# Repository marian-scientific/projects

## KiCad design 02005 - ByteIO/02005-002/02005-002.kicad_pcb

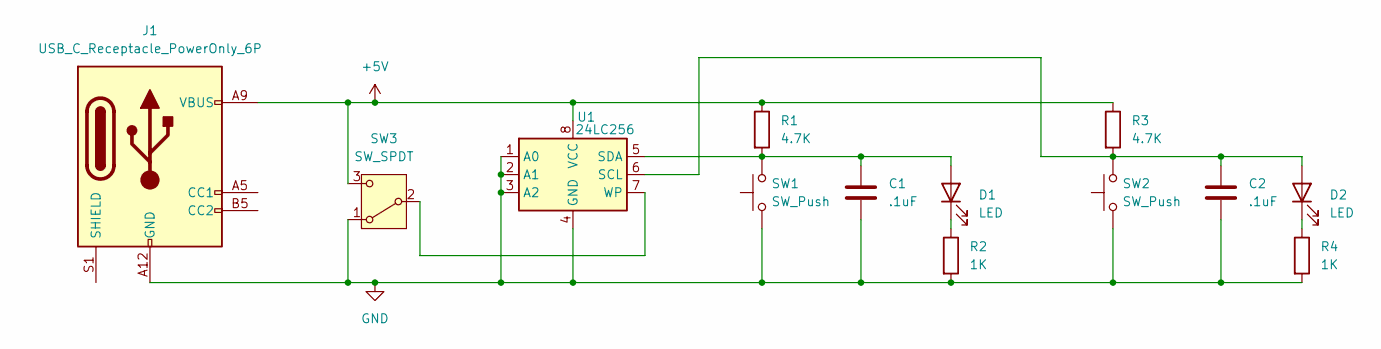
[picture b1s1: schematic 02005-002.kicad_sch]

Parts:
C1, C2: .1uF; C_1206_3216Metric
D1, D2: LED; LED_1206_3216Metric
J1: USB_C_Receptacle_PowerOnly_6P; USB_C_Receptacle_GCT_USB4125-xx-x_6P_TopMnt_Horizontal
R1, R3: 4.7K; R_1206_3216Metric
R2, R4: 1K; R_1206_3216Metric
SW1, SW2: SW_Push; SW_PUSH_6mm_H5mm
SW3: SW_SPDT; SW_Slide-03_Wuerth-WS-SLTV_10x2.5x6.4_P2.54mm
U1: 24LC256; SOIC-8_3.9x4.9mm_P1.27mm

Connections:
+5V: J1.A9 (VBUS), J1.B9 (VBUS), R1.1, R3.1, SW3.3 (C), U1.8 (VCC)
GND: C1.2, C2.2, J1.A12 (GND), J1.B12 (GND), J1.S1 (SHIELD), R2.2, R4.2, SW1.1, SW2.1, SW3.1 (A), U1.1 (A0), U1.2 (A1), U1.3 (A2), U1.4 (GND)
unnamed: C1.1, D1.2 (A), R1.2, SW1.2, U1.5 (SDA)
unnamed: D1.1 (K), R2.1
unnamed: C2.1, D2.2 (A), R3.2, SW2.2, U1.6 (SCL)
unnamed: D2.1 (K), R4.1
unnamed: SW3.2 (B), U1.7 (WP)

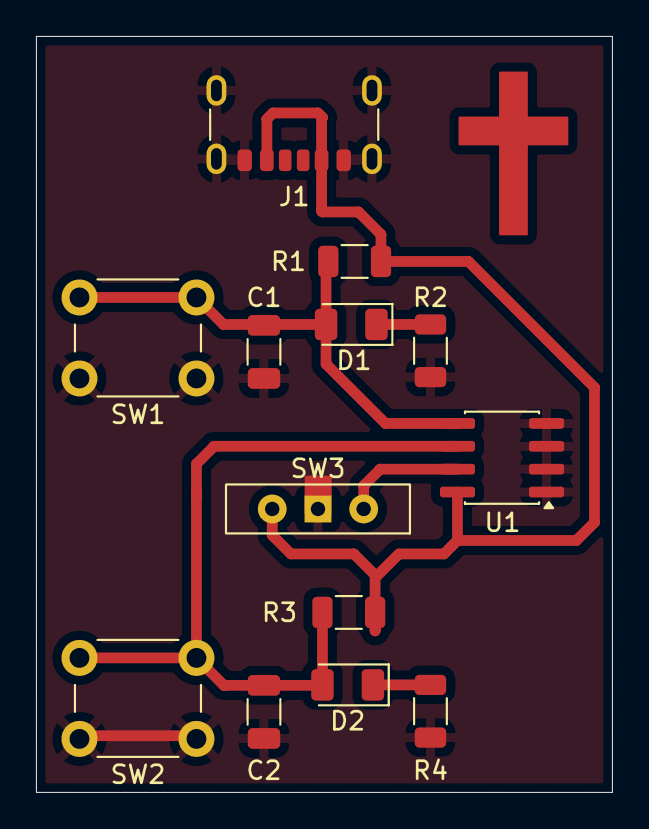
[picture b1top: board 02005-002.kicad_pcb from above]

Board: 2 copper layers, 32.0 x 42.0 mm, 13 parts (0 on the bottom side), 7 nets.

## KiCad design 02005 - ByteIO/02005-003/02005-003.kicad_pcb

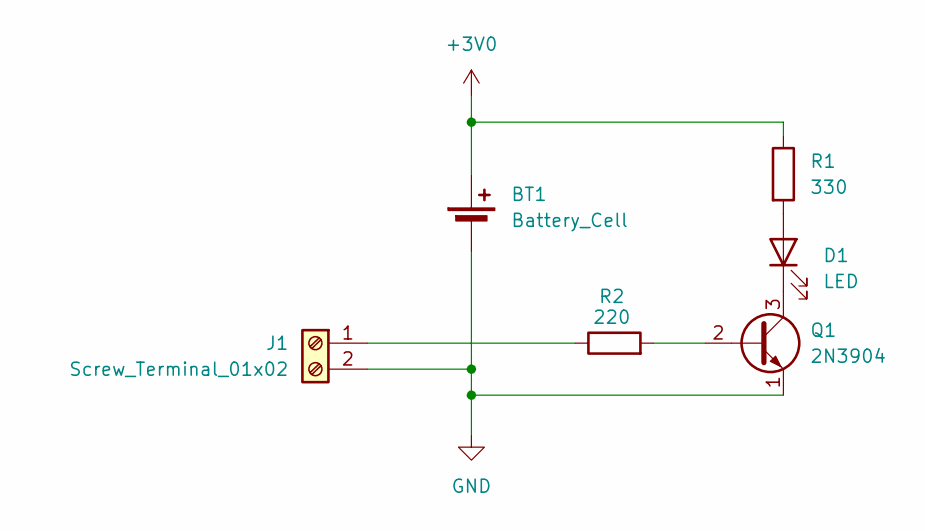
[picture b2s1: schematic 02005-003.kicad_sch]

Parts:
BT1: Battery_Cell; BatteryHolder_Keystone_1058_1x2032
D1: LED; LED_1206_3216Metric
J1: Screw_Terminal_01x02; TerminalBlock_Phoenix_MPT-0,5-2-2.54_1x02_P2.54mm_Horizontal
Q1: 2N3904; SOT-23
R1: 330; R_1206_3216Metric
R2: 220; R_1206_3216Metric

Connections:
+3V0: BT1.1 (+), R1.1
GND: BT1.2 (-), J1.2, Q1.1 (E)
unnamed: D1.2 (A), R1.2
unnamed: D1.1 (K), Q1.3 (C)
unnamed: J1.1, R2.1
unnamed: Q1.2 (B), R2.2

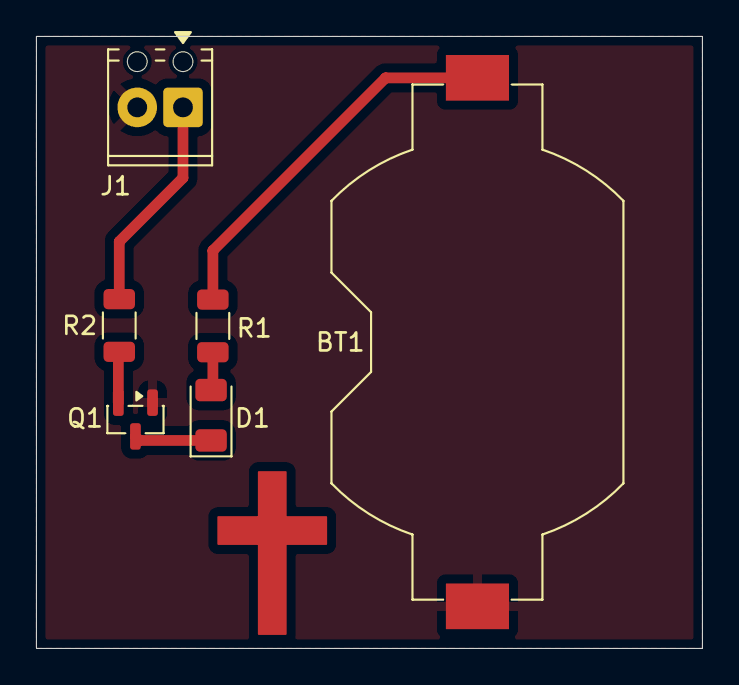
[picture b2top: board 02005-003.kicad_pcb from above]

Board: 2 copper layers, 37.0 x 34.0 mm, 6 parts (0 on the bottom side), 6 nets.

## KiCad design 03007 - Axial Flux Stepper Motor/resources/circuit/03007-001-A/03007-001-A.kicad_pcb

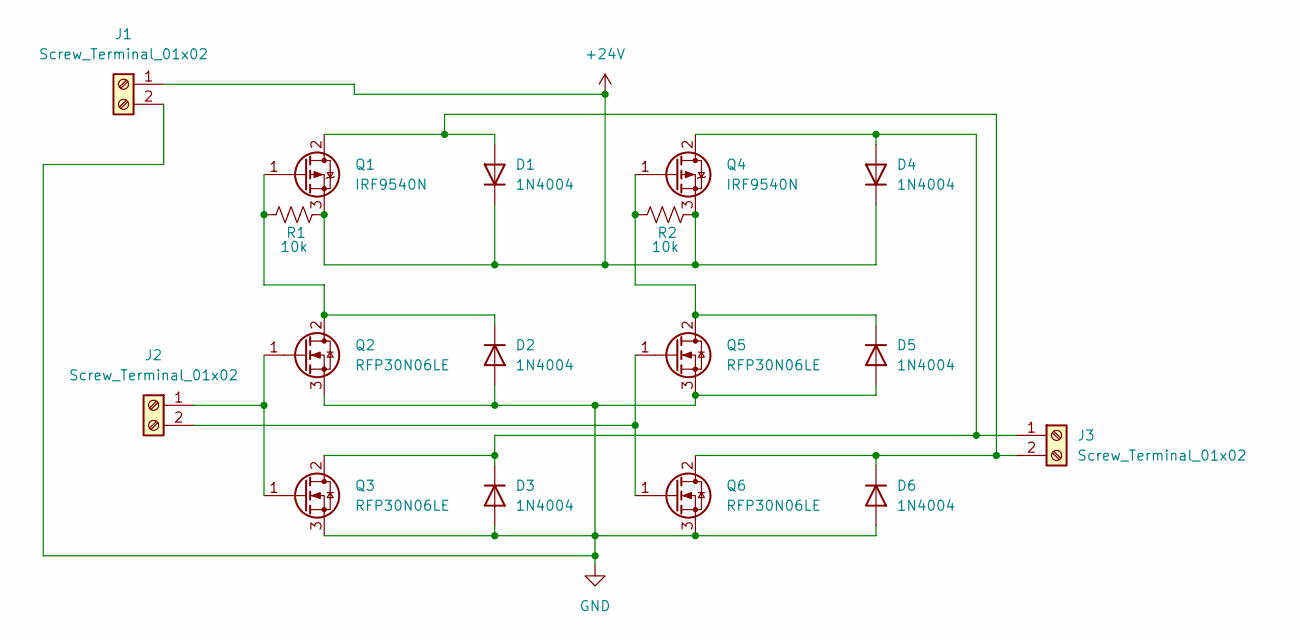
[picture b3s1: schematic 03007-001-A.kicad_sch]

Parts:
D1, D2, D3, D4, D5, D6: 1N4004; D_DO-41_SOD81_P10.16mm_Horizontal
J1, J2, J3: Screw_Terminal_01x02; TerminalBlock_TE_282834-2_1x02_P2.54mm_Horizontal
Q1, Q4: IRF9540N; TO-220-3_Vertical
Q2, Q3, Q5, Q6: RFP30N06LE; TO-220-3_Vertical
R1, R2: 10k; R_Axial_DIN0207_L6.3mm_D2.5mm_P10.16mm_Horizontal

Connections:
+24V: D1.1 (K), D4.1 (K), J1.1, Q1.3 (S), Q4.3 (S), R1.2, R2.2
GND: D2.2 (A), D3.2 (A), D5.2 (A), D6.2 (A), J1.2, Q2.3 (S), Q3.3 (S), Q5.3 (S), Q6.3 (S)
unnamed: D1.2 (A), D6.1 (K), J3.2, Q1.2 (D), Q6.2 (D)
unnamed: D2.1 (K), Q1.1 (G), Q2.2 (D), R1.1
unnamed: D3.1 (K), D4.2 (A), J3.1, Q3.2 (D), Q4.2 (D)
unnamed: D5.1 (K), Q4.1 (G), Q5.2 (D), R2.1
unnamed: J2.1, Q2.1 (G), Q3.1 (G)
unnamed: J2.2, Q5.1 (G), Q6.1 (G)

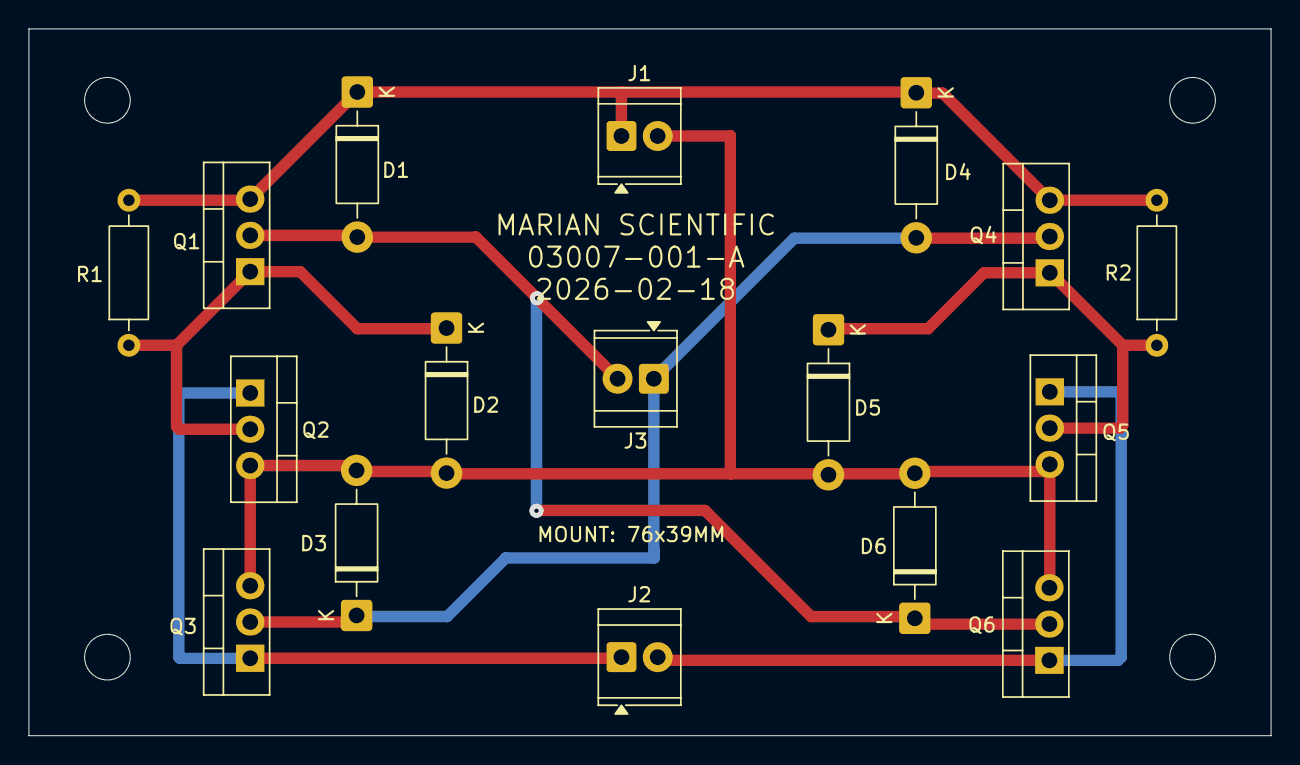
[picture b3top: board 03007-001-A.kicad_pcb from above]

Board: 2 copper layers, 87.0 x 49.5 mm, 17 parts (0 on the bottom side), 8 nets.

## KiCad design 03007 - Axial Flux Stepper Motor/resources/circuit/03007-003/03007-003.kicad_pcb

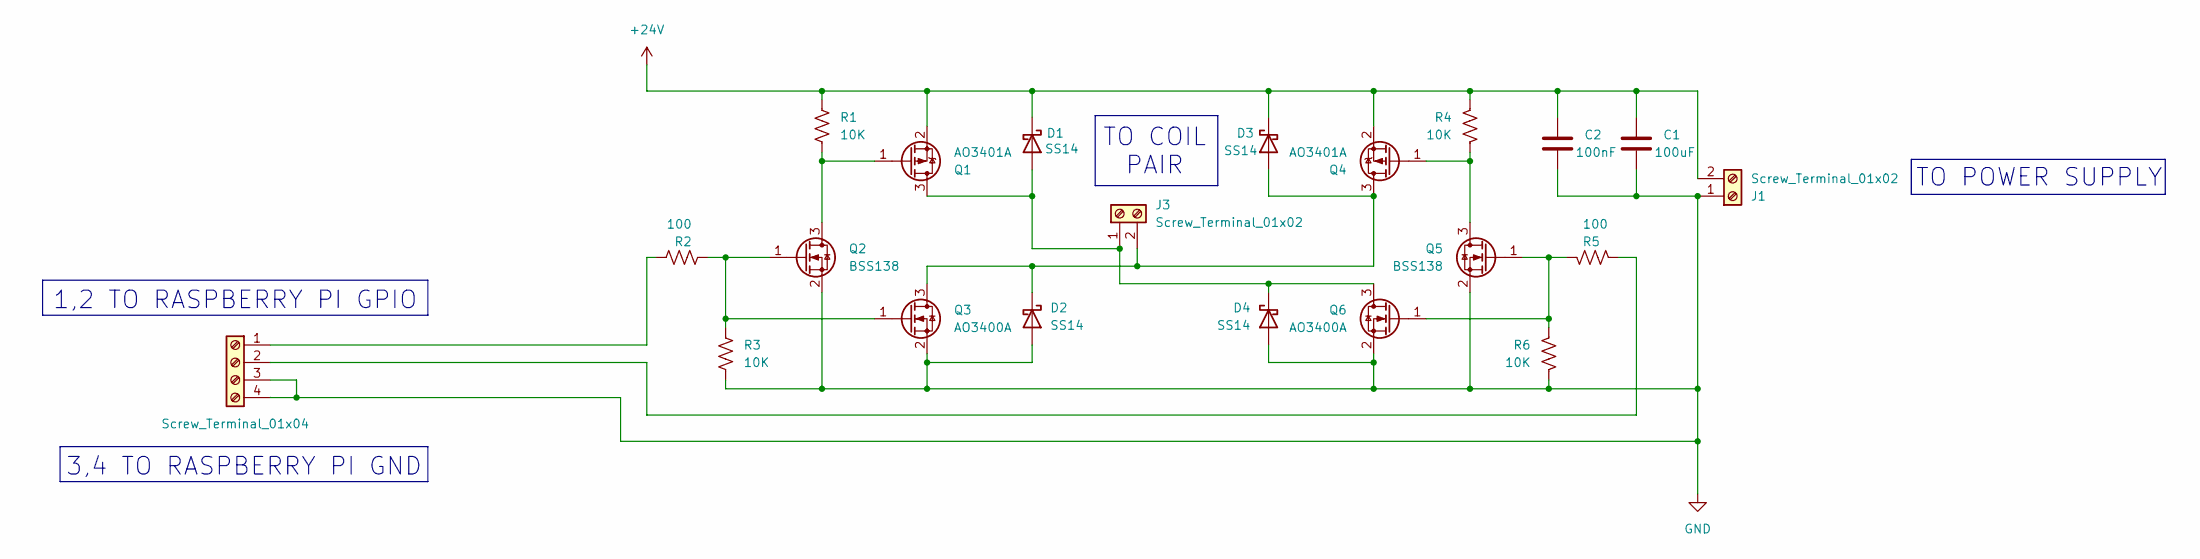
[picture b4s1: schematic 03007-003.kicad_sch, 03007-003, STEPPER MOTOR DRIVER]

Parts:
C1: 100uF; CP_Radial_D5.0mm_P2.50mm
C2: 100nF; C_Disc_D5.0mm_W2.5mm_P2.50mm
D1, D2, D3, D4: SS14; D_SMA
J1, J3: Screw_Terminal_01x02; TerminalBlock_Phoenix_PT-1,5-2-5.0-H_1x02_P5.00mm_Horizontal
J2: Screw_Terminal_01x04; TerminalBlock_Phoenix_MPT-0,5-4-2.54_1x04_P2.54mm_Horizontal
Q1, Q4: AO3401A; SOT-23
Q2, Q5: BSS138; SOT-23
Q3, Q6: AO3400A; SOT-23
R1, R3, R4, R6: 10K; R_1206_3216Metric
R2, R5: 100; R_1206_3216Metric

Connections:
+24V: C1.1, C2.1, D1.1 (K), D3.1 (K), J1.2, Q1.2 (S), Q4.2 (S), R1.1, R4.1
GND: C1.2, C2.2, D2.2 (A), D4.2 (A), J1.1, J2.3, J2.4, Q2.2 (S), Q3.2 (S), Q5.2 (S), Q6.2 (S), R3.2, R6.2
unnamed: D1.2 (A), D4.1 (K), J3.1, Q1.3 (D), Q6.3 (D)
unnamed: D2.1 (K), D3.2 (A), J3.2, Q3.3 (D), Q4.3 (D)
unnamed: J2.1, R2.1
unnamed: J2.2, R5.1
unnamed: Q1.1 (G), Q2.3 (D), R1.2
unnamed: Q2.1 (G), Q3.1 (G), R2.2, R3.1
unnamed: Q4.1 (G), Q5.3 (D), R4.2
unnamed: Q5.1 (G), Q6.1 (G), R5.2, R6.1

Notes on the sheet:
3,4 TO RASPBERRY PI GND
TO COIL PAIR
1,2 TO RASPBERRY PI GPIO
TO POWER SUPPLY

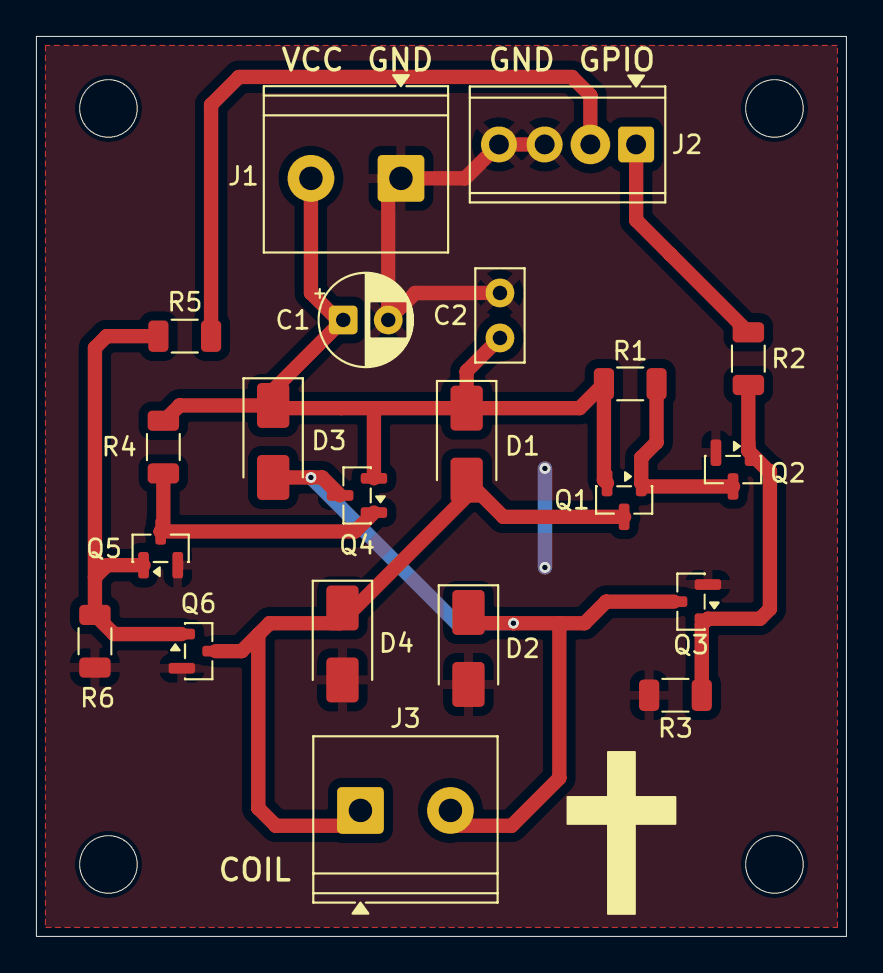
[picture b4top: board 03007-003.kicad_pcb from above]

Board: 2 copper layers, 45.0 x 50.0 mm, 21 parts (0 on the bottom side), 10 nets.

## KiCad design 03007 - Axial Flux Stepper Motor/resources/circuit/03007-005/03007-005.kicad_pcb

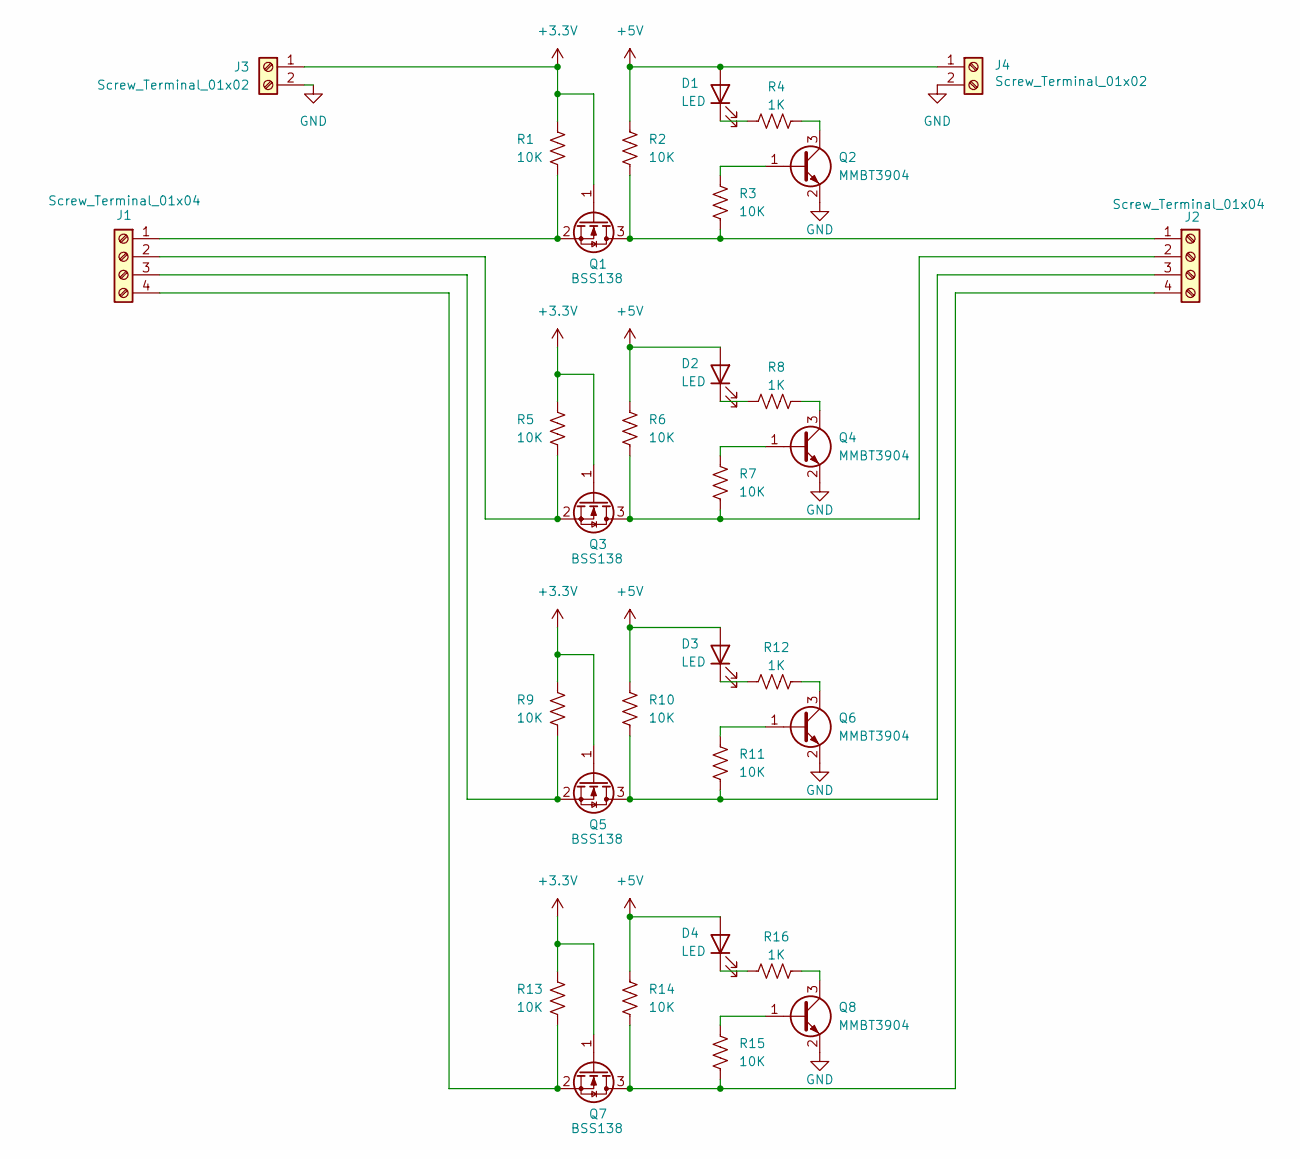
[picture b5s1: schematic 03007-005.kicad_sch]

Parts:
D1, D2, D3, D4: LED; LED_1206_3216Metric
J1, J2: Screw_Terminal_01x04; TerminalBlock_Xinya_XY308-2.54-4P_1x04_P2.54mm_Horizontal
J3, J4: Screw_Terminal_01x02; TerminalBlock_Xinya_XY308-2.54-2P_1x02_P2.54mm_Horizontal
Q1, Q3, Q5, Q7: BSS138; SOT-23
Q2, Q4, Q6, Q8: MMBT3904; SOT-23
R1, R2, R3, R5, R6, R7, R9, R10, R11, R13, R14, R15: 10K; R_1206_3216Metric
R4, R8, R12, R16: 1K; R_1206_3216Metric

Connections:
+3.3V: J3.1, Q1.1 (G), Q3.1 (G), Q5.1 (G), Q7.1 (G), R1.2, R5.2, R9.2, R13.2
+5V: D1.2 (A), D2.2 (A), D3.2 (A), D4.2 (A), J4.1, R2.2, R6.2, R10.2, R14.2
GND: J3.2, J4.2, Q2.2 (E), Q4.2 (E), Q6.2 (E), Q8.2 (E)
unnamed: D1.1 (K), R4.2
unnamed: D2.1 (K), R8.2
unnamed: D3.1 (K), R12.2
unnamed: D4.1 (K), R16.2
unnamed: J1.1, Q1.2 (S), R1.1
unnamed: J1.2, Q3.2 (S), R5.1
unnamed: J1.3, Q5.2 (S), R9.1
unnamed: J1.4, Q7.2 (S), R13.1
unnamed: J2.1, Q1.3 (D), R2.1, R3.1
unnamed: J2.2, Q3.3 (D), R6.1, R7.1
unnamed: J2.3, Q5.3 (D), R10.1, R11.1
unnamed: J2.4, Q7.3 (D), R14.1, R15.1
unnamed: Q2.1 (B), R3.2
unnamed: Q2.3 (C), R4.1
unnamed: Q4.1 (B), R7.2
unnamed: Q4.3 (C), R8.1
unnamed: Q6.1 (B), R11.2
unnamed: Q6.3 (C), R12.1
unnamed: Q8.1 (B), R15.2
unnamed: Q8.3 (C), R16.1

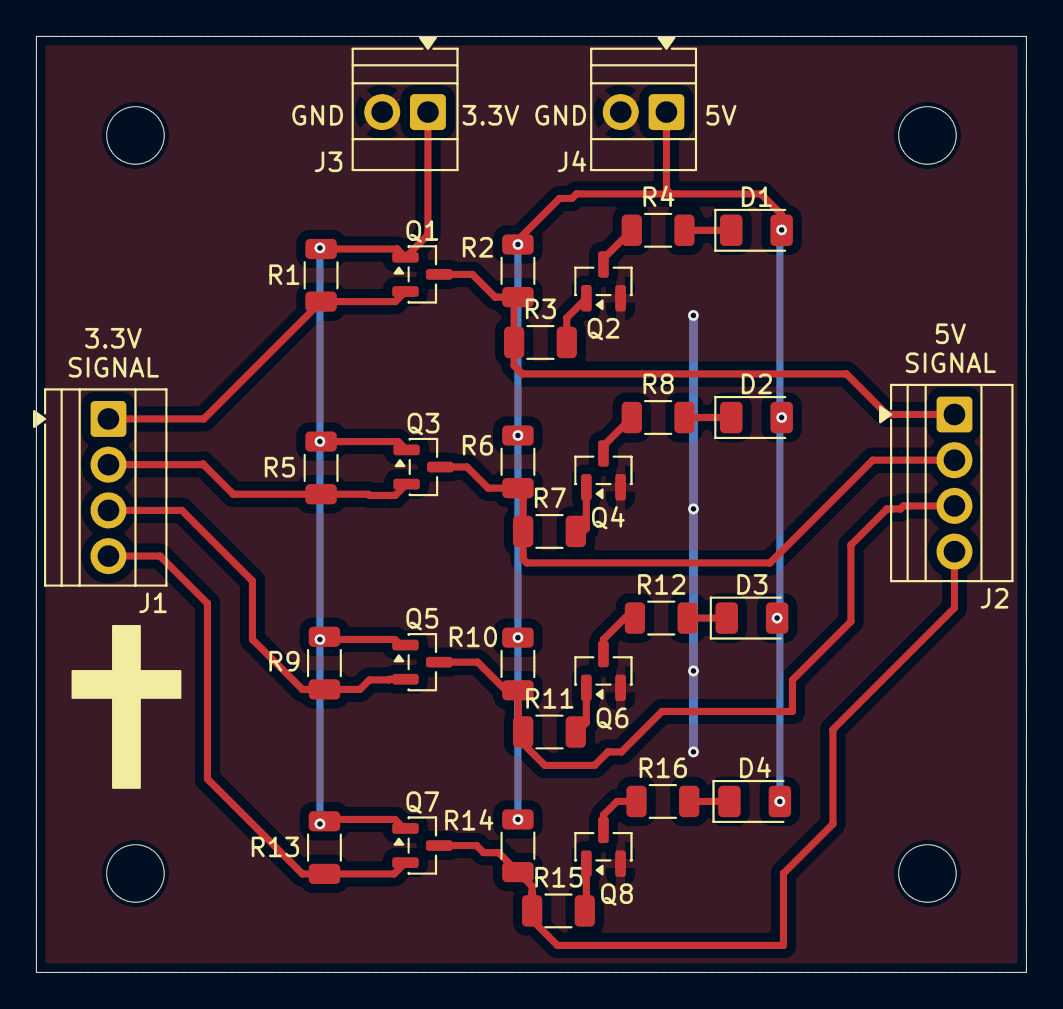
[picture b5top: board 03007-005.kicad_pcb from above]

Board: 2 copper layers, 55.0 x 52.0 mm, 32 parts (0 on the bottom side), 23 nets.

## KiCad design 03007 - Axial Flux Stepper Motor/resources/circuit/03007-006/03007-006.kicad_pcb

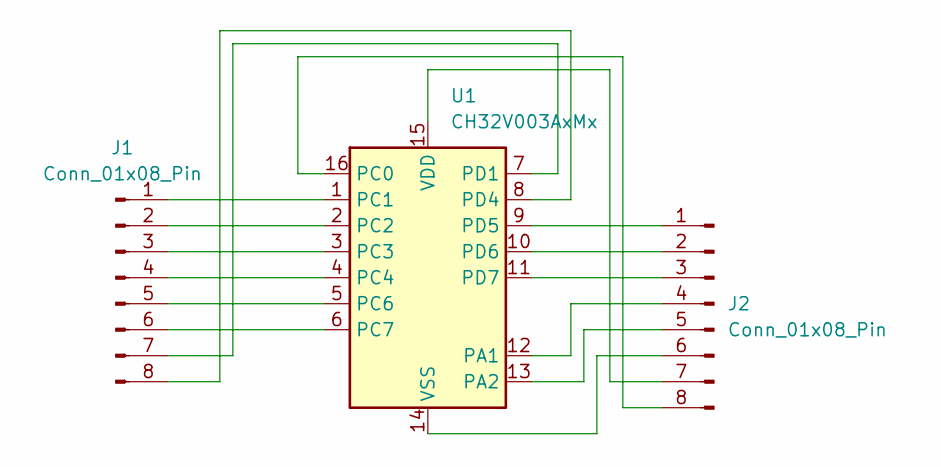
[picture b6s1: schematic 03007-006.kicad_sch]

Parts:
J1, J2: Conn_01x08_Pin; PinHeader_1x08_P2.54mm_Vertical
U1: CH32V003AxMx; STC_SOP-16_3.9x9.9mm_P1.27mm

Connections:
unnamed: J1.1, U1.1 (PC1)
unnamed: J1.2, U1.2 (PC2)
unnamed: J1.3, U1.3 (PC3)
unnamed: J1.4, U1.4 (PC4)
unnamed: J1.5, U1.5 (PC6)
unnamed: J1.6, U1.6 (PC7)
unnamed: J1.7, U1.7 (PD1)
unnamed: J1.8, U1.8 (PD4)
unnamed: J2.1, U1.9 (PD5)
unnamed: J2.2, U1.10 (PD6)
unnamed: J2.3, U1.11 (PD7)
unnamed: J2.4, U1.12 (PA1)
unnamed: J2.5, U1.13 (PA2)
unnamed: J2.6, U1.14 (VSS)
unnamed: J2.7, U1.15 (VDD)
unnamed: J2.8, U1.16 (PC0)

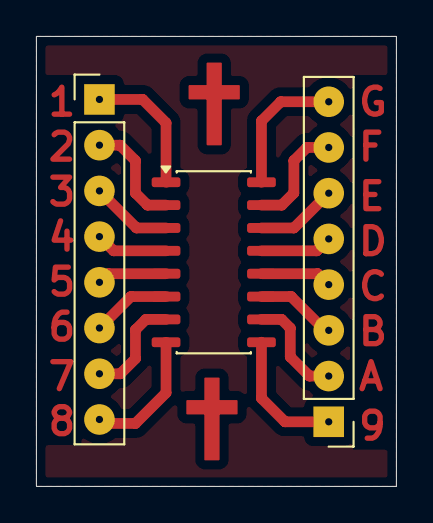
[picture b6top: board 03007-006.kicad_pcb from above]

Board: 2 copper layers, 20.0 x 25.0 mm, 3 parts (0 on the bottom side), 16 nets.

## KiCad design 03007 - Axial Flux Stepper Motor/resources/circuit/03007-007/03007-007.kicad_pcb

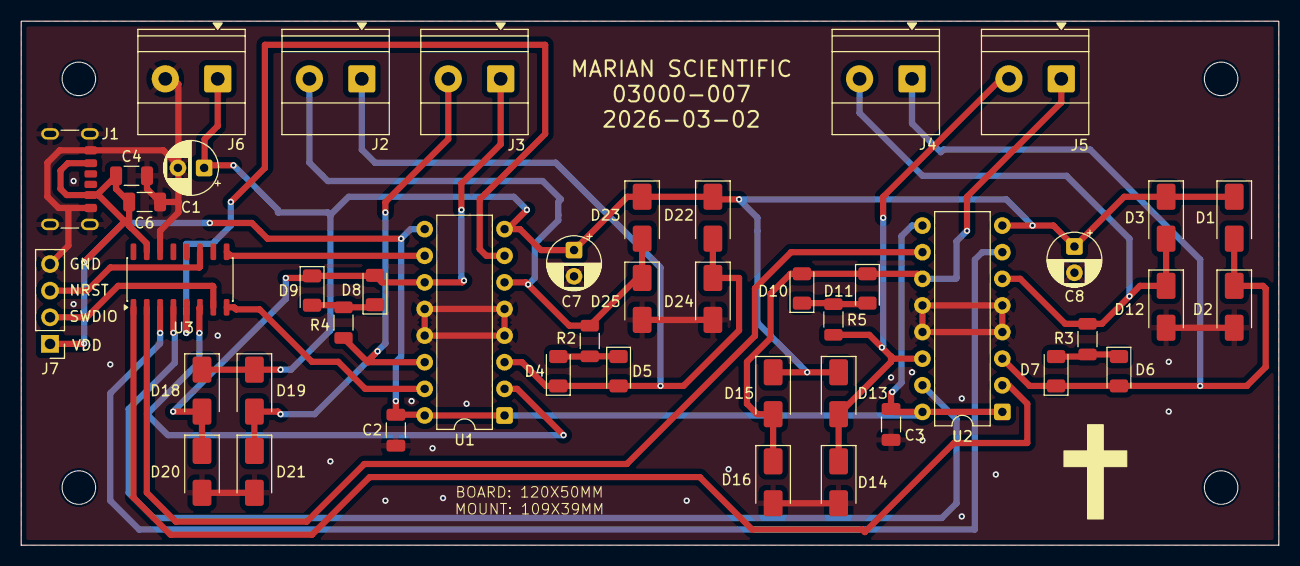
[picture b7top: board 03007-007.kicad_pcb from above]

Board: 2 copper layers, 120.0 x 50.0 mm, 45 parts (0 on the bottom side), 25 nets.

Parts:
C1, C7, C8: 100uF; CP_Radial_D5.0mm_P2.50mm
C2, C3, C6: 100nF; C_1206_3216Metric
C4: 10uF; C_1206_3216Metric
D1, D2, D3, D12, D13, D14, D15, D16, D18, D19, D20, D21, D22, D23, D24, D25: SS14; D_SMA
D4, D5, D6, D7, D8, D9, D10, D11: LED; LED_1206_3216Metric
J1: USB_C_Receptacle_USB2.0_14P; USB_C_Receptacle_GCT_USB4125-xx-x-0190_6P_TopMnt_Horizontal
J2, J3, J4, J5, J6: Screw_Terminal_01x02; TerminalBlock_Phoenix_MKDS-1,5-2_1x02_P5.00mm_Horizontal
J7: Conn_01x04_Pin; PinHeader_1x04_P2.54mm_Vertical
R2, R3, R4, R5: 2K; R_1206_3216Metric
U1, U2: SN754410NE; DIP-16_W7.62mm
U3: CH32V003AxMx; STC_SOP-16_3.9x9.9mm_P1.27mm

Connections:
GND: C1.2, C2.2, C3.2, C4.2, C6.2, C7.2, C8.2, D2.2 (A), D12.2 (A), D14.2 (A), D16.2 (A), D20.2 (A), D21.2 (A), D24.2 (A), D25.2 (A), J1.A12 (GND), J1.B12 (GND), J1.S1 (SHIELD), J6.2, J7.4, U1.4 (GND), U1.5 (GND), U1.12 (GND), U1.13 (GND), U2.4 (GND), U2.5 (GND), U2.12 (GND), U2.13 (GND), U3.14 (VSS)
unnamed: D1.2 (A), D2.1 (K), D6.2 (A), D7.1 (K), J4.1, U2.3 (1Y)
unnamed: D4.2 (A), D5.1 (K), R2.1
unnamed: D6.1 (K), D7.2 (A), R3.1
unnamed: D8.1 (K), D9.2 (A), R4.1
unnamed: D10.2 (A), D11.1 (K), D15.2 (A), D16.1 (K), J5.1, U2.11 (3Y)
unnamed: D10.1 (K), D11.2 (A), R5.1
unnamed: D3.2 (A), D12.1 (K), J4.2, R3.2, U2.6 (2Y)
unnamed: D13.2 (A), D14.1 (K), J5.2, R5.2, U2.14 (4Y)
unnamed: D8.2 (A), D9.1 (K), D18.2 (A), D20.1 (K), J3.1, U1.11 (3Y)
unnamed: D19.2 (A), D21.1 (K), J3.2, R4.2, U1.14 (4Y)
unnamed: D4.1 (K), D5.2 (A), D22.2 (A), D24.1 (K), J2.1, U1.3 (1Y)
unnamed: D23.2 (A), D25.1 (K), J2.2, R2.2, U1.6 (2Y)
unnamed: C2.1, C3.1, C4.1, C6.1, J1.A9 (VBUS), J1.B9 (VBUS), J7.1, U1.1 (1,2EN), U1.9 (3,4EN), U1.16 (VCC1), U2.1 (1,2EN), U2.9 (3,4EN), U2.16 (VCC1), U3.15 (VDD)
unnamed: J7.2, U3.7 (PD1)
unnamed: J7.3, U3.11 (PD7)
unnamed: U1.2 (1A), U3.6 (PC7)
unnamed: U1.7 (2A), U3.5 (PC6)
unnamed: U1.10 (3A), U3.9 (PD5)
unnamed: U1.15 (4A), U3.8 (PD4)
unnamed: U2.2 (1A), U3.1 (PC1)
unnamed: U2.7 (2A), U3.3 (PC3)
unnamed: U2.10 (3A), U3.2 (PC2)
unnamed: U2.15 (4A), U3.4 (PC4)
Vdrive: C1.1, C7.1, C8.1, D1.1 (K), D3.1 (K), D13.1 (K), D15.1 (K), D18.1 (K), D19.1 (K), D22.1 (K), D23.1 (K), J6.1, U1.8 (VCC2), U2.8 (VCC2)
